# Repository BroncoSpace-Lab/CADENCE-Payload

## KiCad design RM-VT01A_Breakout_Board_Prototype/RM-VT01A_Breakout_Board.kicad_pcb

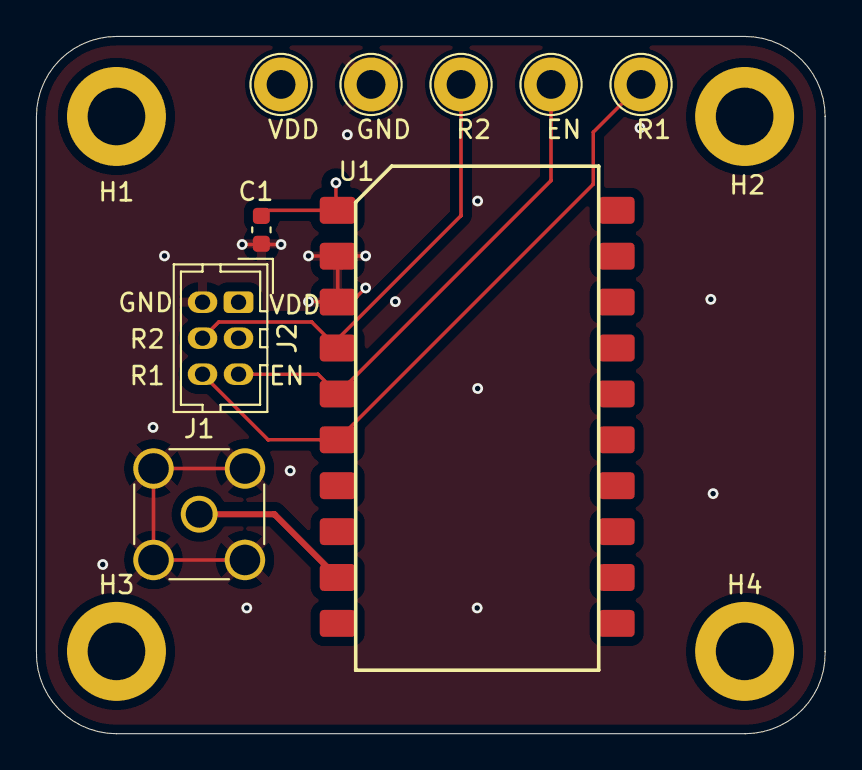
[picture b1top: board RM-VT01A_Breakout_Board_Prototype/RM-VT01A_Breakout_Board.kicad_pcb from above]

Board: 4 copper layers, 43.8 x 38.7 mm, 13 parts (0 on the bottom side), 6 nets.

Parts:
C1: 10uF; C_0603_1608Metric
EN: TestPoint; TestPoint_Loop_D2.60mm_Drill1.6mm_Beaded
GND: TestPoint; TestPoint_Loop_D2.60mm_Drill1.6mm_Beaded
H1, H2, H3, H4: MountingHole; MountingHole_3.2mm_M3_ISO14580_Pad
J1: Conn_Coaxial; SMA_Amphenol_132291_Vertical
J2: Conn_01x06; PinHeader_2x03_P2.00mm_Vertical
R1, R2: TestPoint; TestPoint_Loop_D2.60mm_Drill1.6mm_Beaded
U1: RM-VT01-A
VDD: TestPoint; TestPoint_Loop_D2.60mm_Drill1.6mm_Beaded

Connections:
CTRL_EN: EN.1, J2.5, U1.5 (CTRL_EN)
CTRL_R1: J2.6, R1.1, U1.6 (CTRL_R1)
CTRL_R2: J2.4, R2.1, U1.4 (CTRL_R2)
GND: C1.2, GND.1, J1.2 (Ext), J2.2, U1.2 (GND), U1.3 (GND)
unnamed: J1.1 (In), U1.9 (RADFET_OUT)
VDD: C1.1, J2.1, U1.1 (Vdd), VDD.1

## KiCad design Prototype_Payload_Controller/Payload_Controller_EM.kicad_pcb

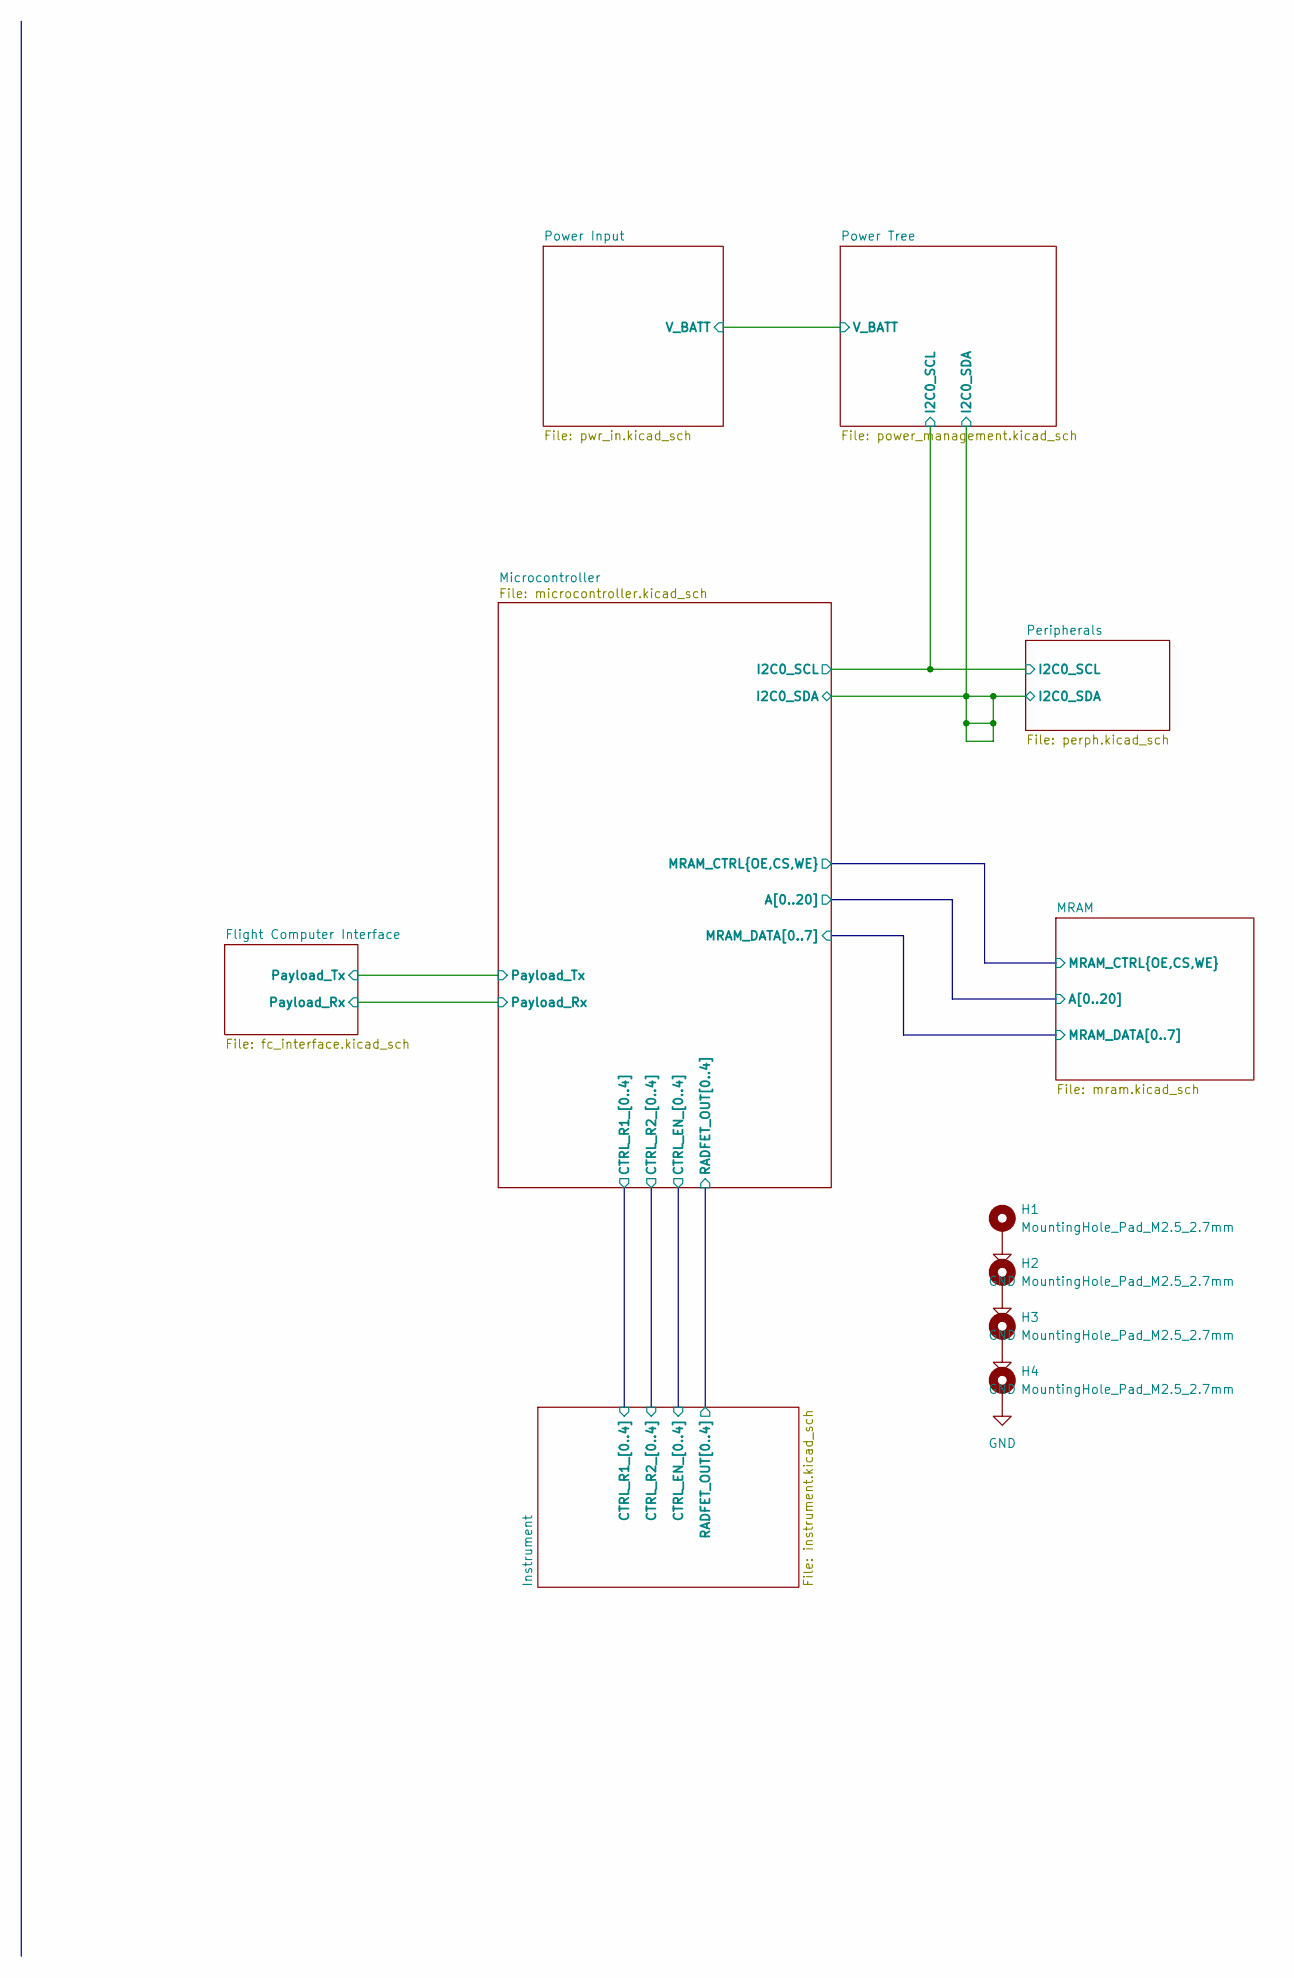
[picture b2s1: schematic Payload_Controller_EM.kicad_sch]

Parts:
H1, H2, H3, H4: MountingHole_Pad_M2.5_2.7mm; MountingHole_2.7mm_M2.5_DIN965_Pad

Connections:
GND: H1.1 (MP), H2.1 (MP), H3.1 (MP), H4.1 (MP); also elsewhere on the board

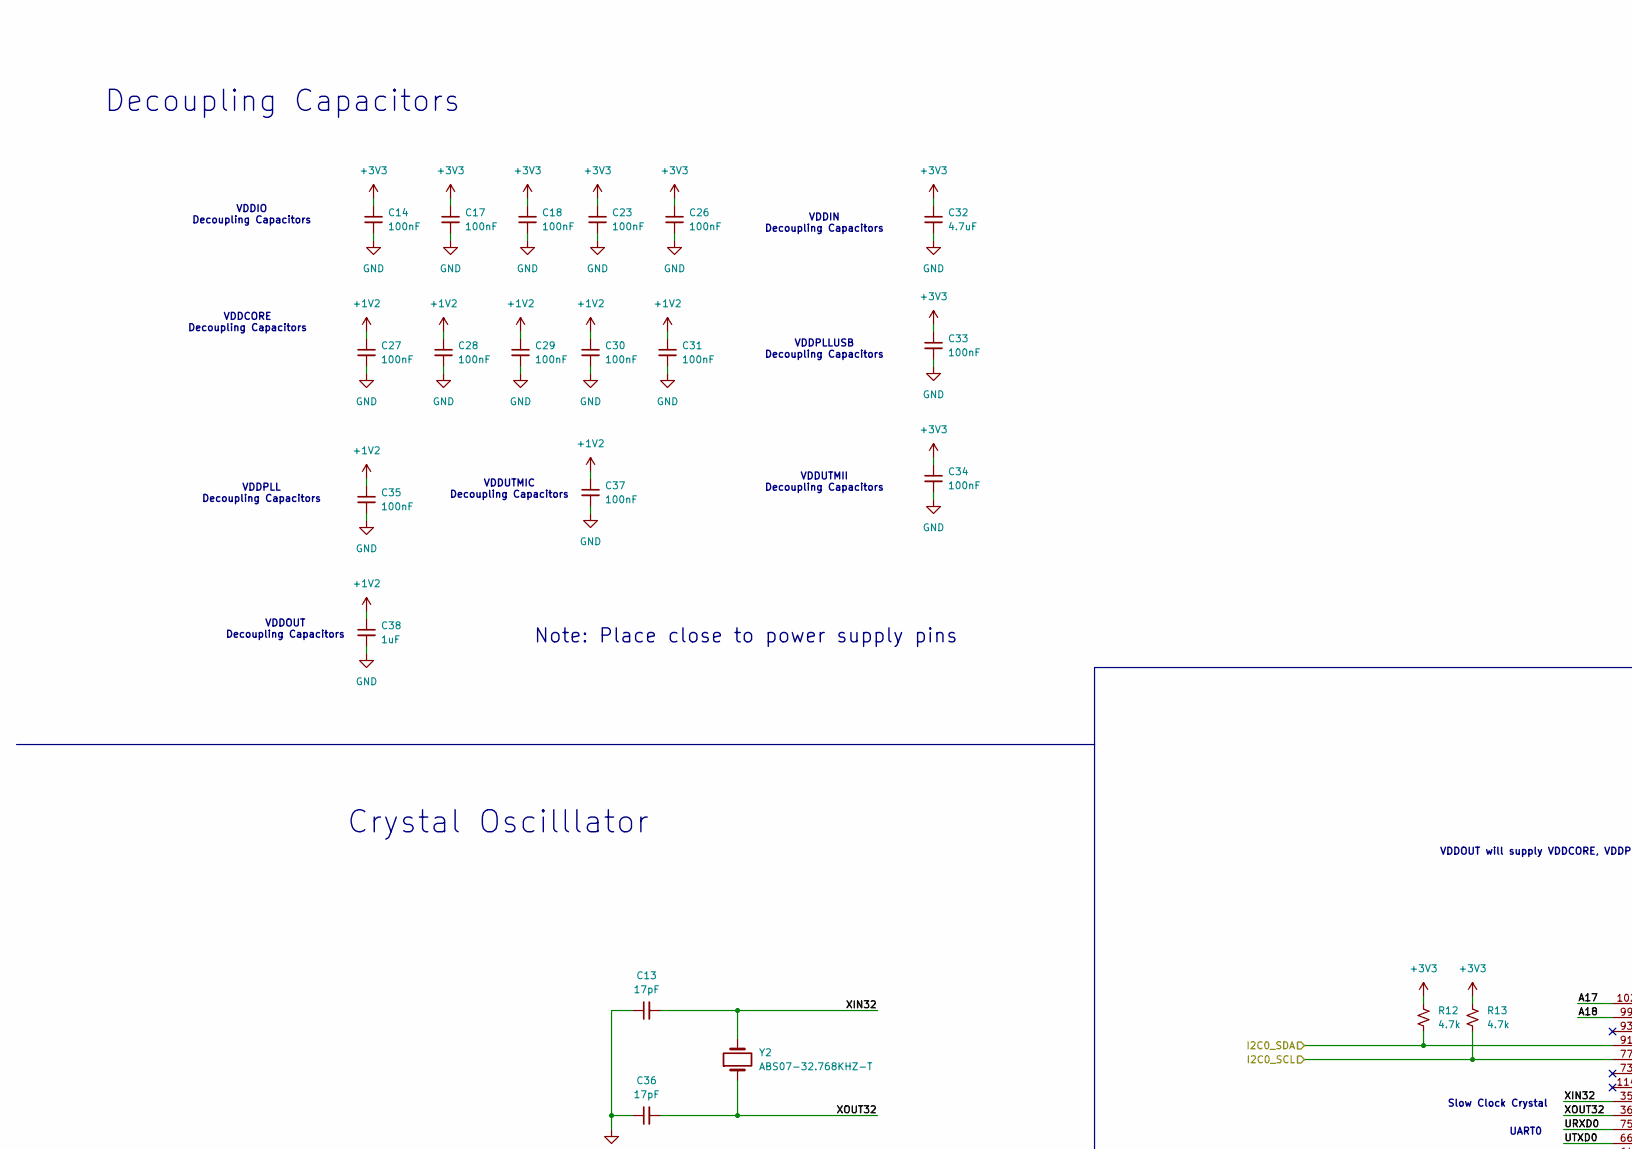
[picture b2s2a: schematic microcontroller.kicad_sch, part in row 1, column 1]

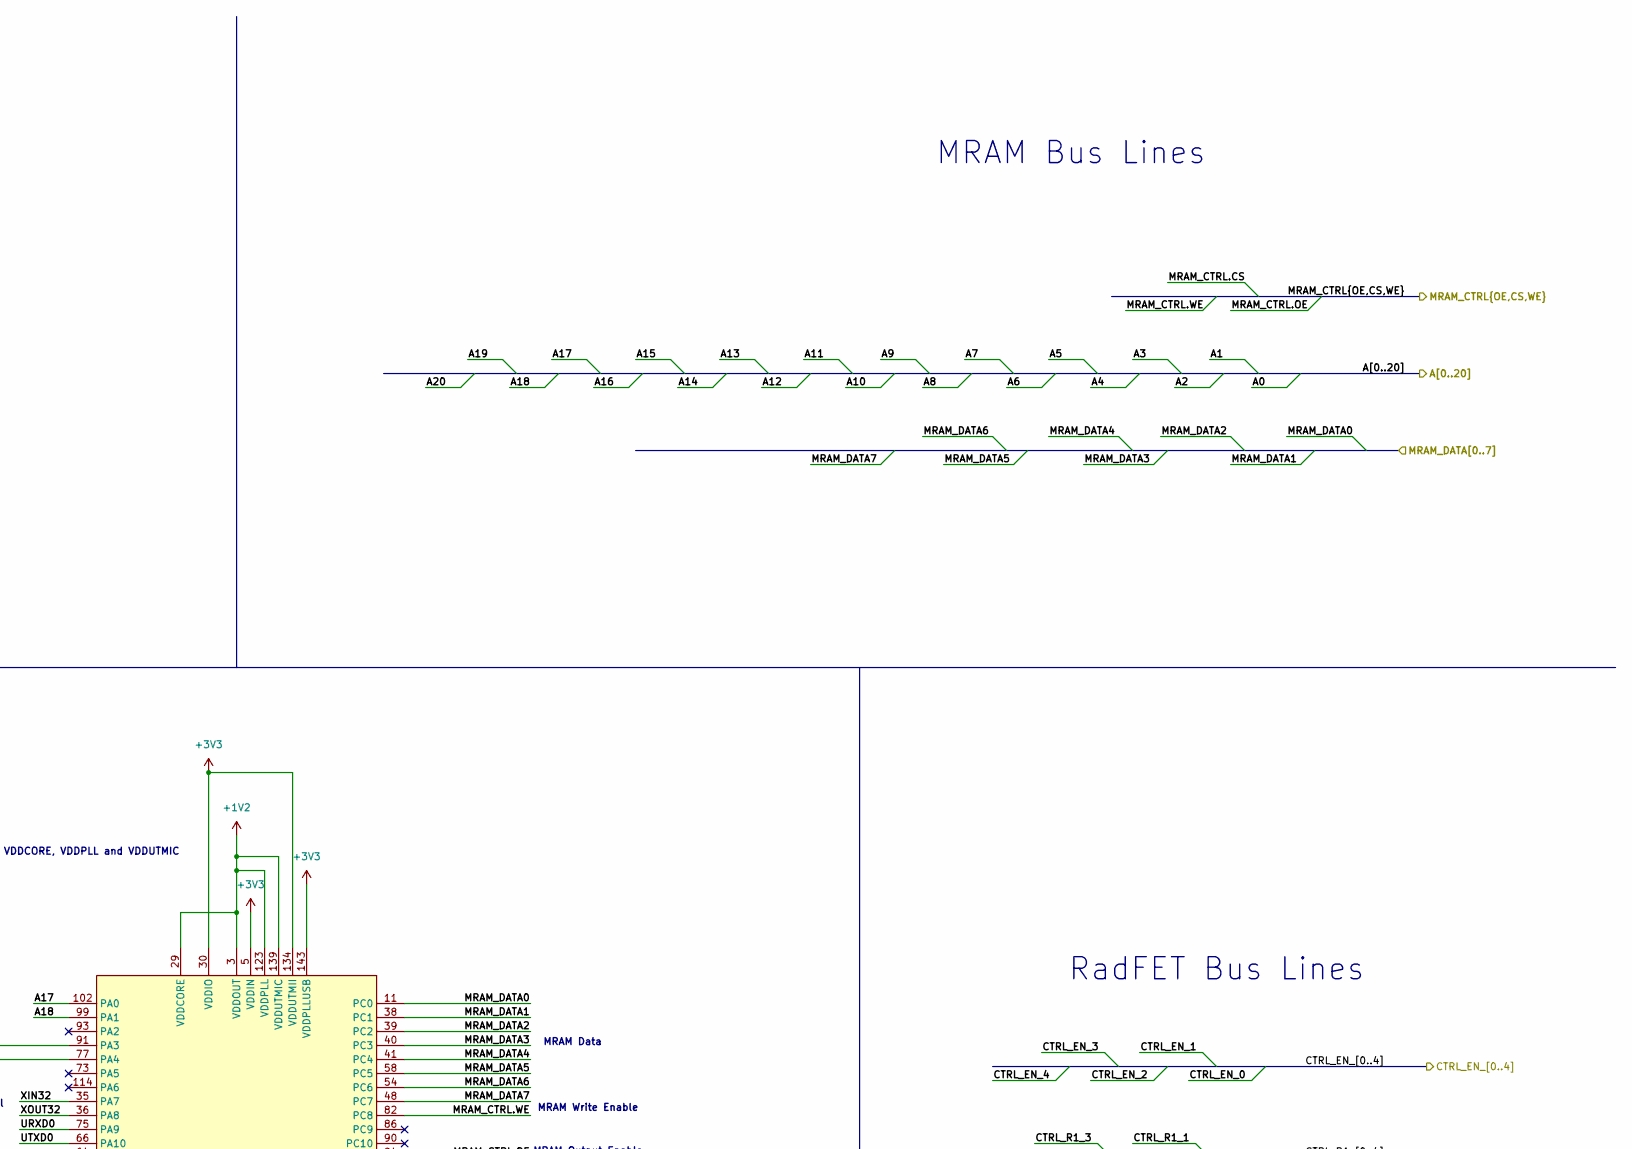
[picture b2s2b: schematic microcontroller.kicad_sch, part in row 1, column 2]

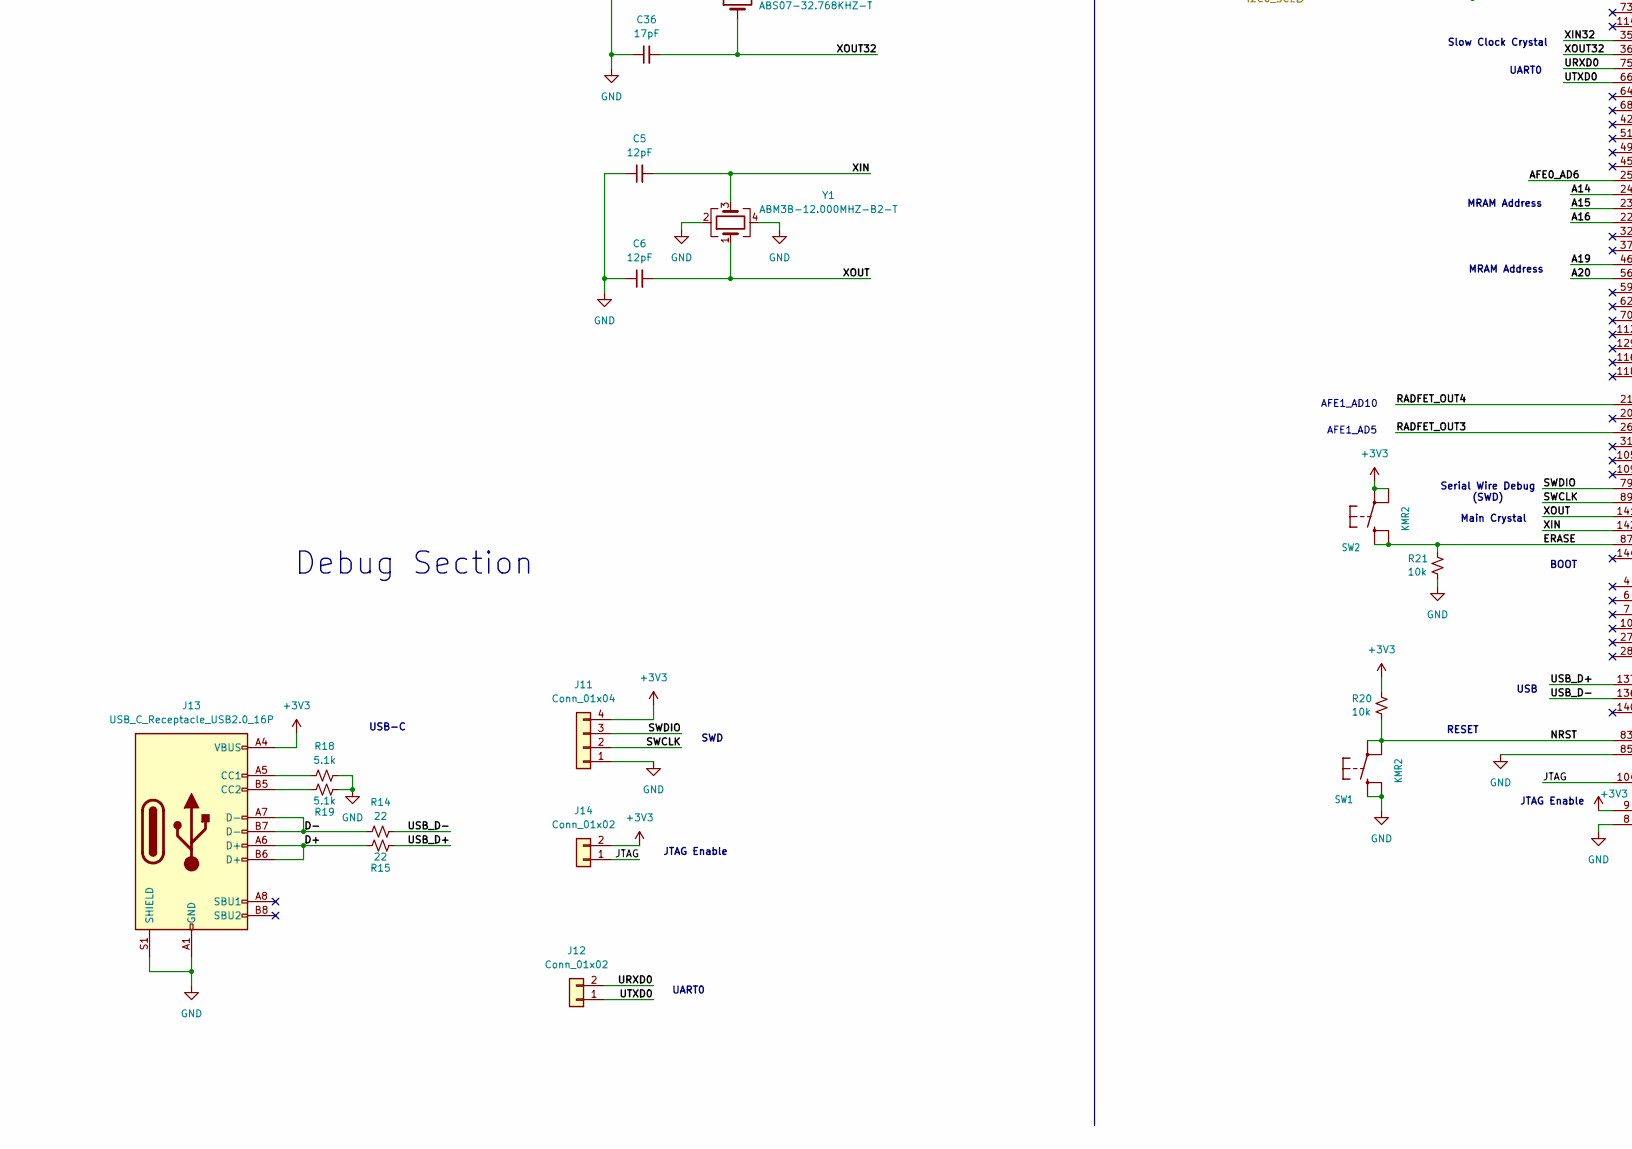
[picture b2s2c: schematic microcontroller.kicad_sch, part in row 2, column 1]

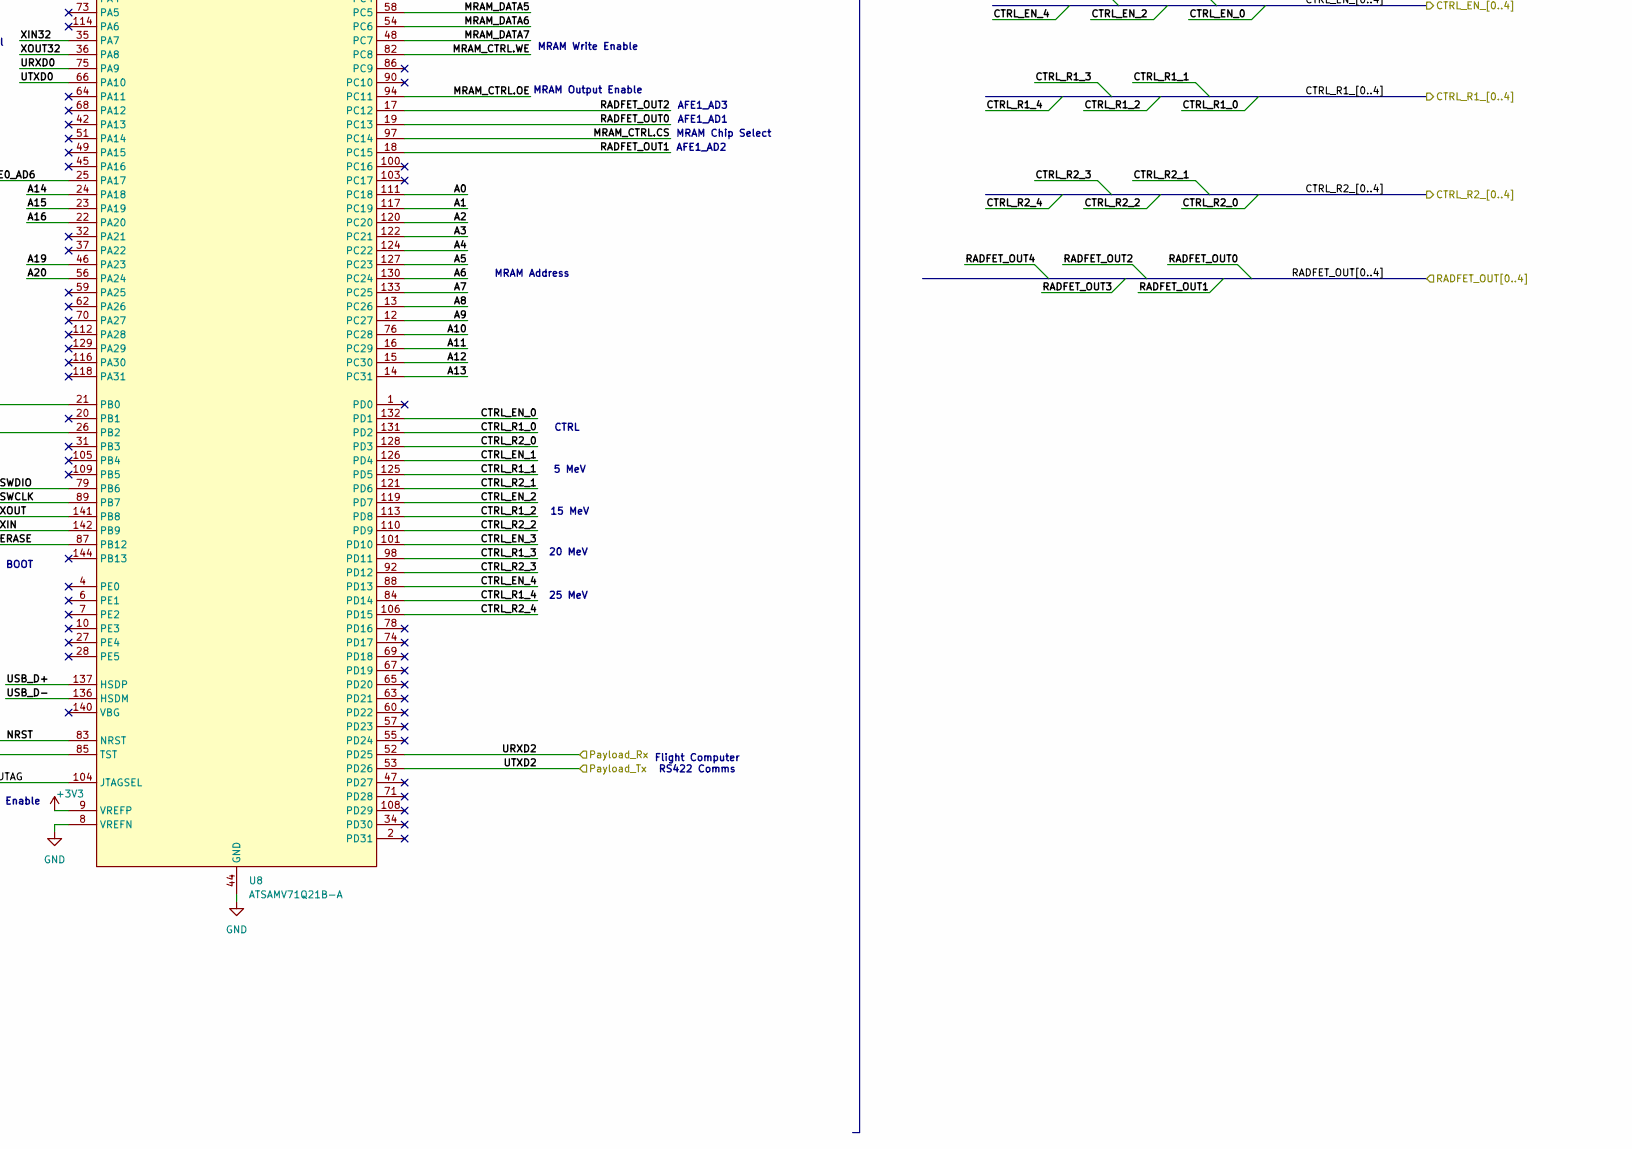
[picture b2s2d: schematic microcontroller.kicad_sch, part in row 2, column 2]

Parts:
C5, C6: 12pF; C_0402_1005Metric
C13, C36: 17pF; C_0402_1005Metric
C14, C17, C18: 100nF; R_0402_1005Metric
C23, C26, C27, C28, C29, C30, C31, C33, C34, C35, C37: 100nF; C_0402_1005Metric
C32: 4.7uF; C_0603_1608Metric
C38: 1uF; C_0603_1608Metric
J11: Conn_01x04; PinHeader_1x04_P2.54mm_Vertical
J12, J14: Conn_01x02; PinHeader_1x02_P2.54mm_Vertical
J13: USB_C_Receptacle_USB2.0_16P; USB_C_Receptacle_HRO_TYPE-C-31-M-12
R12, R13: 4.7k; R_0603_1608Metric
R14, R15: 22; R_0603_1608Metric
R18, R19: 5.1k; R_0603_1608Metric
R20, R21: 10k; R_0603_1608Metric
SW1, SW2: KMR2; BTN_KMR2_4.6X2.8
U8: ATSAMV71Q21B-A; LQFP-144_20x20mm_P0.5mm
Y1: ABM3B-12.000MHZ-B2-T; Crystal_SMD_3225-4Pin_3.2x2.5mm
Y2: ABS07-32.768KHZ-T; Crystal_SMD_3215-2Pin_3.2x1.5mm

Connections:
+1V2: C27.1, C28.1, C29.1, C30.1, C31.1, C35.1, C37.1, C38.1, U8.3 (VDDOUT), U8.29 (VDDCORE), U8.33 (VDDCORE), U8.50 (VDDCORE), U8.81 (VDDCORE), U8.107 (VDDCORE), U8.123 (VDDPLL), U8.139 (VDDUTMIC)
+3V3: C14.1, C17.1, C18.1, C23.1, C26.1, C32.1, C33.1, C34.1, J11.4, J13.A4 (VBUS), J13.A9 (VBUS), J13.B4 (VBUS), J13.B9 (VBUS), J14.2, R12.1, R13.1, R20.1, SW2.A, SW2.A' (P1), U8.5 (VDDIN), U8.9 (VREFP), U8.30 (VDDIO), U8.43 (VDDIO), U8.72 (VDDIO), U8.80 (VDDIO), U8.96 (VDDIO), U8.134 (VDDUTMII), U8.143 (VDDPLLUSB); also elsewhere on the board
/Instrument/CTRL_EN_0: U8.132 (PD1); also elsewhere on the board
/Instrument/CTRL_EN_1: U8.126 (PD4); also elsewhere on the board
/Instrument/CTRL_EN_2: U8.119 (PD7); also elsewhere on the board
/Instrument/CTRL_EN_3: U8.101 (PD10); also elsewhere on the board
/Instrument/CTRL_EN_4: U8.88 (PD13); also elsewhere on the board
/Instrument/CTRL_R1_0: U8.131 (PD2); also elsewhere on the board
/Instrument/CTRL_R1_1: U8.125 (PD5); also elsewhere on the board
/Instrument/CTRL_R1_2: U8.113 (PD8); also elsewhere on the board
/Instrument/CTRL_R1_3: U8.98 (PD11); also elsewhere on the board
/Instrument/CTRL_R1_4: U8.84 (PD14); also elsewhere on the board
/Instrument/CTRL_R2_0: U8.128 (PD3); also elsewhere on the board
/Instrument/CTRL_R2_1: U8.121 (PD6); also elsewhere on the board
/Instrument/CTRL_R2_2: U8.110 (PD9); also elsewhere on the board
/Instrument/CTRL_R2_3: U8.92 (PD12); also elsewhere on the board
/Instrument/CTRL_R2_4: U8.106 (PD15); also elsewhere on the board
/Instrument/RADFET_OUT0: U8.19 (PC13); also elsewhere on the board
/Instrument/RADFET_OUT1: U8.18 (PC15); also elsewhere on the board
/Instrument/RADFET_OUT2: U8.17 (PC12); also elsewhere on the board
/Instrument/RADFET_OUT3: U8.26 (PB2); also elsewhere on the board
/Instrument/RADFET_OUT4: U8.21 (PB0); also elsewhere on the board
/MRAM/A0: U8.111 (PC18); also elsewhere on the board
/MRAM/A1: U8.117 (PC19); also elsewhere on the board
/MRAM/A2: U8.120 (PC20); also elsewhere on the board
/MRAM/A3: U8.122 (PC21); also elsewhere on the board
/MRAM/A4: U8.124 (PC22); also elsewhere on the board
/MRAM/A5: U8.127 (PC23); also elsewhere on the board
/MRAM/A6: U8.130 (PC24); also elsewhere on the board
/MRAM/A7: U8.133 (PC25); also elsewhere on the board
/MRAM/A8: U8.13 (PC26); also elsewhere on the board
/MRAM/A9: U8.12 (PC27); also elsewhere on the board
/MRAM/A10: U8.76 (PC28); also elsewhere on the board
/MRAM/A11: U8.16 (PC29); also elsewhere on the board
/MRAM/A12: U8.15 (PC30); also elsewhere on the board
/MRAM/A13: U8.14 (PC31); also elsewhere on the board
/MRAM/A14: U8.24 (PA18); also elsewhere on the board
/MRAM/A15: U8.23 (PA19); also elsewhere on the board
/MRAM/A16: U8.22 (PA20); also elsewhere on the board
/MRAM/A17: U8.102 (PA0); also elsewhere on the board
/MRAM/A18: U8.99 (PA1); also elsewhere on the board
/MRAM/A19: U8.46 (PA23); also elsewhere on the board
/MRAM/A20: U8.56 (PA24); also elsewhere on the board
/MRAM/MRAM_CTRL.CS: U8.97 (PC14); also elsewhere on the board
/MRAM/MRAM_CTRL.OE: U8.94 (PC11); also elsewhere on the board
/MRAM/MRAM_CTRL.WE: U8.82 (PC8); also elsewhere on the board
/MRAM/MRAM_DATA0: U8.11 (PC0); also elsewhere on the board
/MRAM/MRAM_DATA1: U8.38 (PC1); also elsewhere on the board
/MRAM/MRAM_DATA2: U8.39 (PC2); also elsewhere on the board
/MRAM/MRAM_DATA3: U8.40 (PC3); also elsewhere on the board
/MRAM/MRAM_DATA4: U8.41 (PC4); also elsewhere on the board
/MRAM/MRAM_DATA5: U8.58 (PC5); also elsewhere on the board
/MRAM/MRAM_DATA6: U8.54 (PC6); also elsewhere on the board
/MRAM/MRAM_DATA7: U8.48 (PC7); also elsewhere on the board
/Microcontroller/AFE0_AD6: U8.25 (PA17)
/Microcontroller/D+: J13.A6 (D+), J13.B6 (D+), R15.1
/Microcontroller/D-: J13.A7 (D-), J13.B7 (D-), R14.2
/Microcontroller/ERASE: R21.1, SW2.B (S), SW2.B' (S1), U8.87 (PB12)
/Microcontroller/JTAG: J14.1, U8.104 (JTAGSEL)
/Microcontroller/NRST: R20.2, SW1.A, SW1.A' (P1), U8.83 (NRST)
/Microcontroller/SWCLK: J11.2, U8.89 (PB7)
/Microcontroller/SWDIO: J11.3, U8.79 (PB6)
/Microcontroller/URXD0: J12.2, U8.75 (PA9)
/Microcontroller/URXD2: U8.52 (PD25); also elsewhere on the board
/Microcontroller/USB_D+: R15.2, U8.137 (HSDP)
/Microcontroller/USB_D-: R14.1, U8.136 (HSDM)
/Microcontroller/UTXD0: J12.1, U8.66 (PA10)
/Microcontroller/UTXD2: U8.53 (PD26); also elsewhere on the board
/Microcontroller/XIN: C5.2, U8.142 (PB9), Y1.3
/Microcontroller/XIN32: C13.2, U8.35 (PA7), Y2.2
/Microcontroller/XOUT: C6.2, U8.141 (PB8), Y1.1
/Microcontroller/XOUT32: C36.2, U8.36 (PA8), Y2.1
/Peripherals/I2C0_SCL: R13.2, U8.77 (PA4); also elsewhere on the board
/Peripherals/I2C0_SDA: R12.2, U8.91 (PA3); also elsewhere on the board
GND: C5.1, C6.1, C13.1, C14.2, C17.2, C18.2, C23.2, C26.2, C27.2, C28.2, C29.2, C30.2, C31.2, C32.2, C33.2, C34.2, C35.2, C36.1, C37.2, C38.2, J11.1, J13.A1 (GND), J13.A12 (GND), J13.B1 (GND), J13.B12 (GND), J13.S1 (SHIELD), R18.1, R19.2, R21.2, SW1.B (S), SW1.B' (S1), U8.8 (VREFN), U8.44 (GND), U8.61 (GND), U8.85 (TST), U8.95 (GND), U8.115 (GND), U8.135 (GND), U8.138 (GND), Y1.2, Y1.4; also elsewhere on the board
unnamed: J13.A5 (CC1), R18.2
unnamed: J13.B5 (CC2), R19.1

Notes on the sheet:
CTRL
VDDUTMIC Decoupling Capacitors
JTAG Enable
AFE1_AD10
MRAM Output Enable
Crystal Oscilllator
MRAM Chip Select
Note: Place close to power supply pins
20 MeV
VDDPLL Decoupling Capacitors
RESET
MRAM Write Enable
VDDIO Decoupling Capacitors
MRAM Address
RadFET Bus Lines
Debug Section
15 MeV
Flight Computer RS422 Comms
MRAM Data
VDDOUT Decoupling Capacitors
AFE1_AD5
VDDOUT will supply VDDCORE, VDDPLL and VDDUTMIC
25 MeV
AFE1_AD2
Main Crystal
VDDUTMII Decoupling Capacitors
UART0
USB-C
Decoupling Capacitors
MRAM Bus Lines
BOOT
AFE1_AD1
Slow Clock Crystal
AFE1_AD3
VDDCORE Decoupling Capacitors
VDDIN Decoupling Capacitors
SWD
5 MeV
VDDPLLUSB Decoupling Capacitors
USB

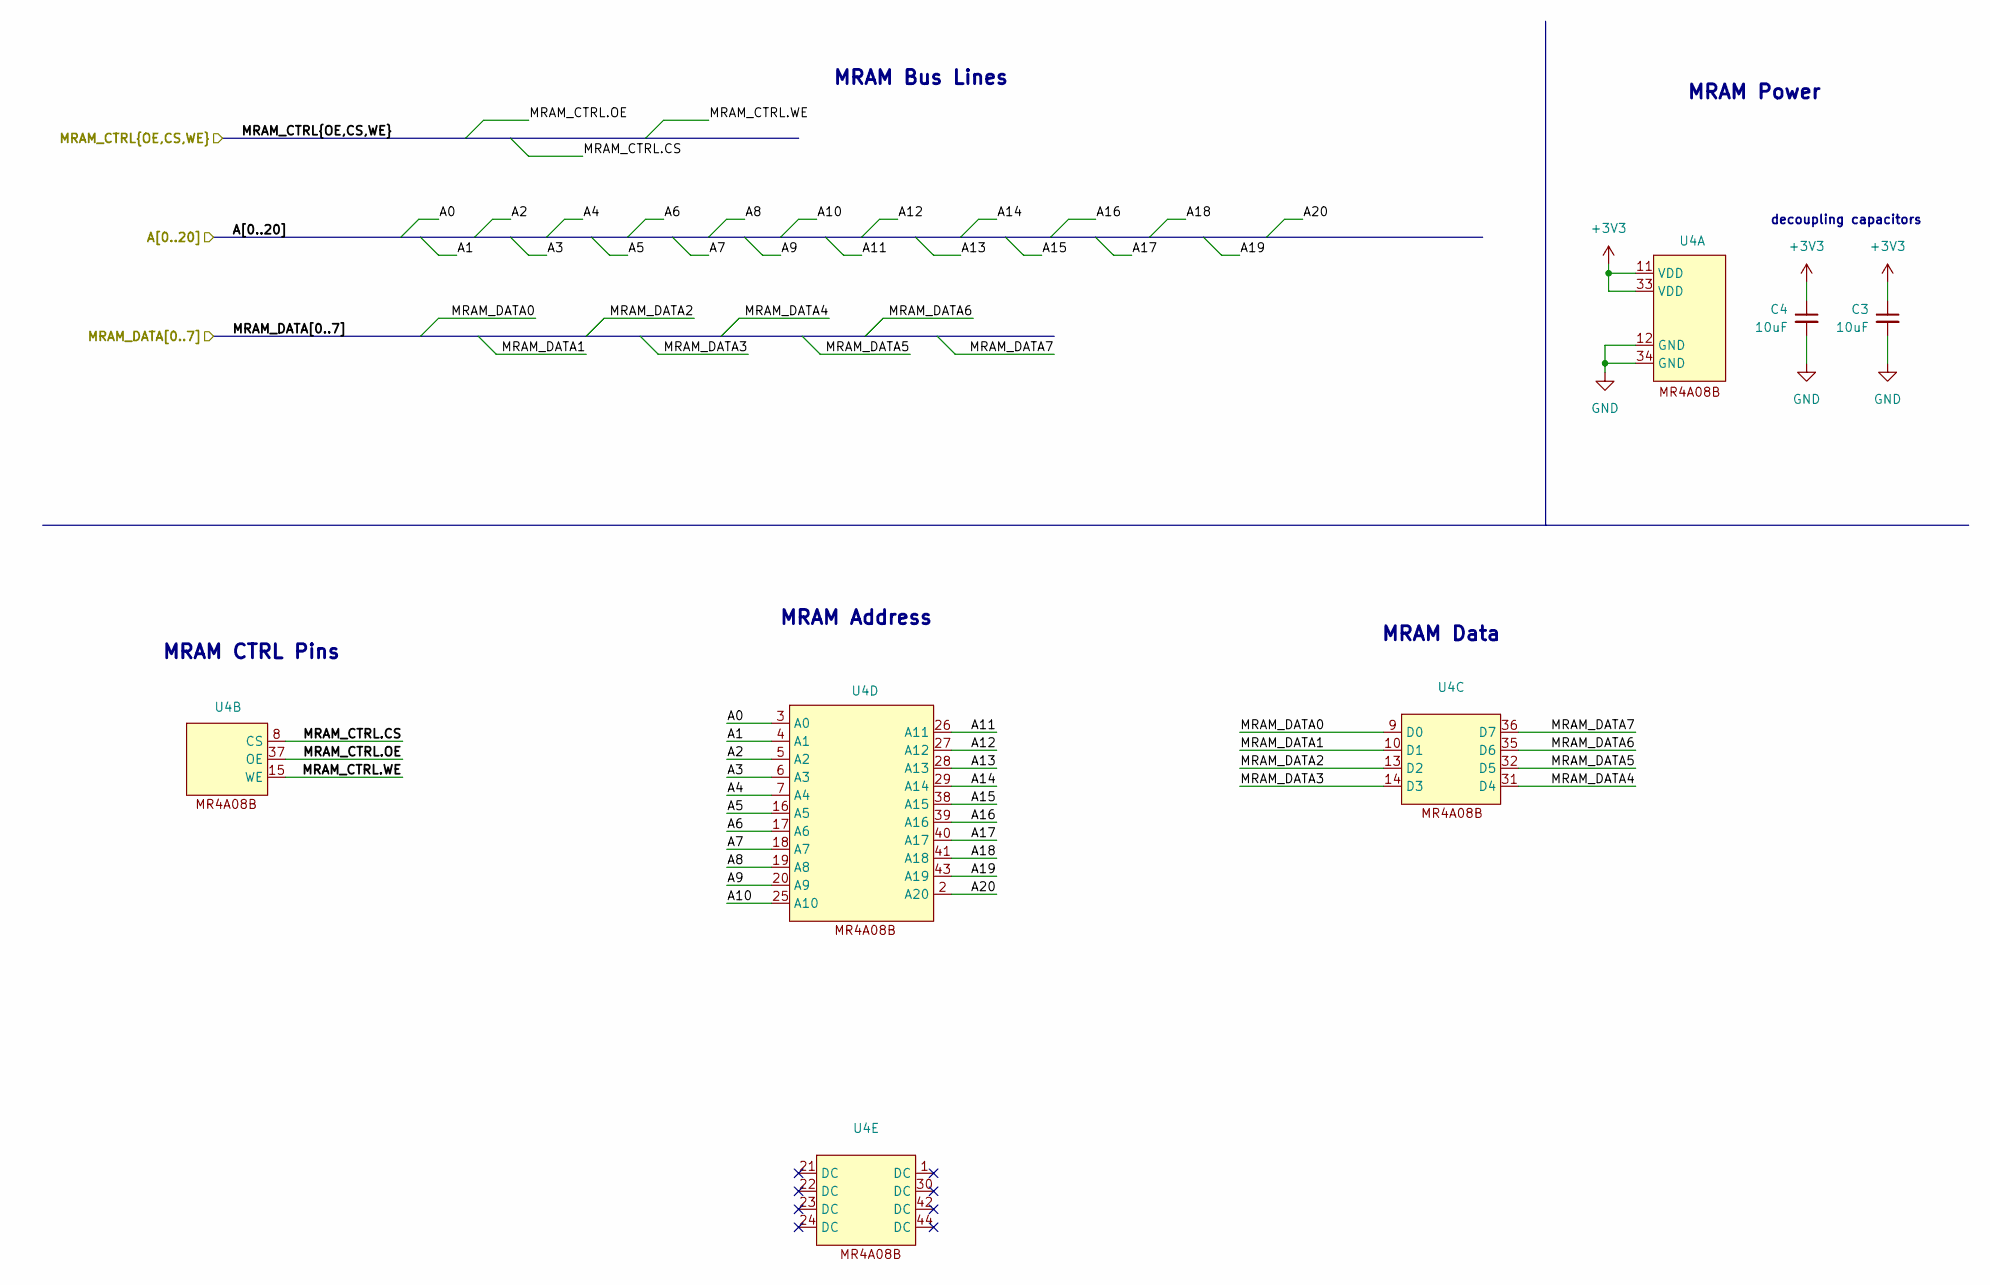
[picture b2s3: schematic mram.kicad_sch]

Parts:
C3, C4: 10uF; C_0603_1608Metric
U4: TSOP-II-44_10.16x18.41mm_P0.8mm

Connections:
+3V3: C3.1, C4.1, U4.11 (VDD), U4.33 (VDD); also elsewhere on the board
/MRAM/A0: U4.3 (A0); also elsewhere on the board
/MRAM/A1: U4.4 (A1); also elsewhere on the board
/MRAM/A2: U4.5 (A2); also elsewhere on the board
/MRAM/A3: U4.6 (A3); also elsewhere on the board
/MRAM/A4: U4.7 (A4); also elsewhere on the board
/MRAM/A5: U4.16 (A5); also elsewhere on the board
/MRAM/A6: U4.17 (A6); also elsewhere on the board
/MRAM/A7: U4.18 (A7); also elsewhere on the board
/MRAM/A8: U4.19 (A8); also elsewhere on the board
/MRAM/A9: U4.20 (A9); also elsewhere on the board
/MRAM/A10: U4.25 (A10); also elsewhere on the board
/MRAM/A11: U4.26 (A11); also elsewhere on the board
/MRAM/A12: U4.27 (A12); also elsewhere on the board
/MRAM/A13: U4.28 (A13); also elsewhere on the board
/MRAM/A14: U4.29 (A14); also elsewhere on the board
/MRAM/A15: U4.38 (A15); also elsewhere on the board
/MRAM/A16: U4.39 (A16); also elsewhere on the board
/MRAM/A17: U4.40 (A17); also elsewhere on the board
/MRAM/A18: U4.41 (A18); also elsewhere on the board
/MRAM/A19: U4.43 (A19); also elsewhere on the board
/MRAM/A20: U4.2 (A20); also elsewhere on the board
/MRAM/MRAM_CTRL.CS: U4.8 (CS); also elsewhere on the board
/MRAM/MRAM_CTRL.OE: U4.37 (OE); also elsewhere on the board
/MRAM/MRAM_CTRL.WE: U4.15 (WE); also elsewhere on the board
/MRAM/MRAM_DATA0: U4.9 (D0); also elsewhere on the board
/MRAM/MRAM_DATA1: U4.10 (D1); also elsewhere on the board
/MRAM/MRAM_DATA2: U4.13 (D2); also elsewhere on the board
/MRAM/MRAM_DATA3: U4.14 (D3); also elsewhere on the board
/MRAM/MRAM_DATA4: U4.31 (D4); also elsewhere on the board
/MRAM/MRAM_DATA5: U4.32 (D5); also elsewhere on the board
/MRAM/MRAM_DATA6: U4.35 (D6); also elsewhere on the board
/MRAM/MRAM_DATA7: U4.36 (D7); also elsewhere on the board
GND: C3.2, C4.2, U4.12 (GND), U4.34 (GND); also elsewhere on the board

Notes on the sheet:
MRAM Power
MRAM Bus Lines
decoupling capacitors
MRAM Data
MRAM Address
MRAM CTRL Pins

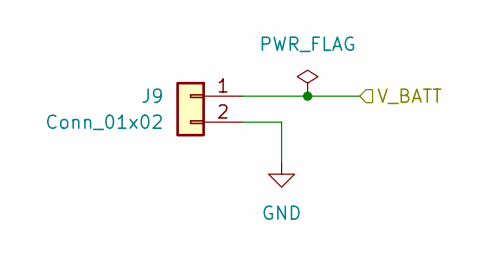
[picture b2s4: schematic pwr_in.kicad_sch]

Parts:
J9: Conn_01x02; AMASS_XT60-F_1x02_P7.20mm_Vertical

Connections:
GND: J9.2; also elsewhere on the board
VBAT: J9.1; also elsewhere on the board

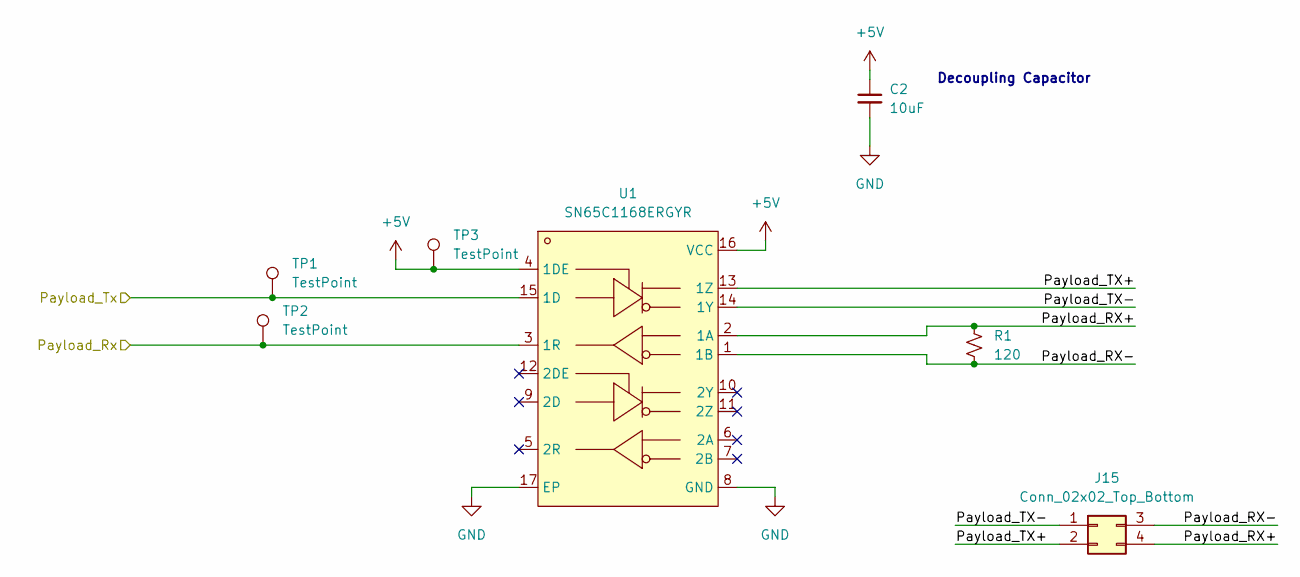
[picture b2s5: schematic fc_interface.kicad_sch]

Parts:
C2: 10uF; C_0603_1608Metric
J15: Conn_02x02_Top_Bottom; Hirose_DF11-4DP-2DSA_2x02_P2.00mm_Vertical
R1: 120; R_0603_1608Metric
TP1, TP2, TP3: TestPoint; TestPoint_Pad_1.0x1.0mm
U1: SN65C1168ERGYR; SOP-16_4.55x10.3mm_P1.27mm; LCSC Part C201679

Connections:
+5V: C2.1, TP3.1, U1.4 (1DE), U1.16 (VCC); also elsewhere on the board
/Flight Computer Interface/Payload_RX+: J15.4, R1.1, U1.2 (1A)
/Flight Computer Interface/Payload_RX-: J15.3, R1.2, U1.1 (1B)
/Flight Computer Interface/Payload_TX+: J15.2, U1.13 (1Z)
/Flight Computer Interface/Payload_TX-: J15.1, U1.14 (1Y)
/Microcontroller/URXD2: TP2.1, U1.3 (1R); also elsewhere on the board
/Microcontroller/UTXD2: TP1.1, U1.15 (1D); also elsewhere on the board
GND: C2.2, U1.8 (GND), U1.17 (EP); also elsewhere on the board

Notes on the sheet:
Decoupling Capacitor
